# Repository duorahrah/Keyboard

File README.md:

# Custom 75% Mechanical Keyboard
Designed and built fully custom mechanical keyboard end-to-end, PCB design (KiCad), case design (Onshape) and 3D printing, and firmware (QMK on RP2040).\

## PCB Design

<br/>
-	Designed a RP2040-based custom mechanical keyboard PCB in KiCad with full keyboard matrix and USB-C connectivity
-	Includes full RP2040 support circuitry (crystal, QSPI flash, decoupling, reset and BOOTSEL)
-	Routed and manufactured the PCB

## Case Design

<br/>
-	Modeled custom case in Onshape, accounting for PCB mounting points, USB-C cutout, and switch plate clearance 

## Firmware
-	Developed custom QMK firmware for the keyboard, including multi-layer keymap and matrix/layout configuration to match the custom PCB design

## Challenges
-	USB and RP2040 debugging – I encountered an issue where the keyboard could not be detected by my computer while trying to flash the firmware. I was able to identify the issue as a short between the D+/D- connections through systematic multimeter-based debugging and fix it.
-	3D printer calibration - Case was printed using secondhand ELEGOO Neptune 4 Max, a printer which is known to be finnicky. I did research and looked at experiences from others who had the same printer to learn how to properly calibrate the printer, including replacing the bed springs with silicon spacers, and altering the printer’s configuration file to automatically level the bed and generate a printing mesh. 
-	Obtaining tools and materials – I was unable to gain access to public/free 3D printers over the summer, so I purchased a secondhand printer off Facebook Marketplace. The PCB and parts were ordered from JLCPCB and DigiKey (including $40 for international shipping D:). 

## Results
-	Successfully designed, manufactured, and assembled a working mechanical keyboard for daily use
-	Gained experience across PCB design, mechanical design, manufacturing, firmware development, and hardware debugging

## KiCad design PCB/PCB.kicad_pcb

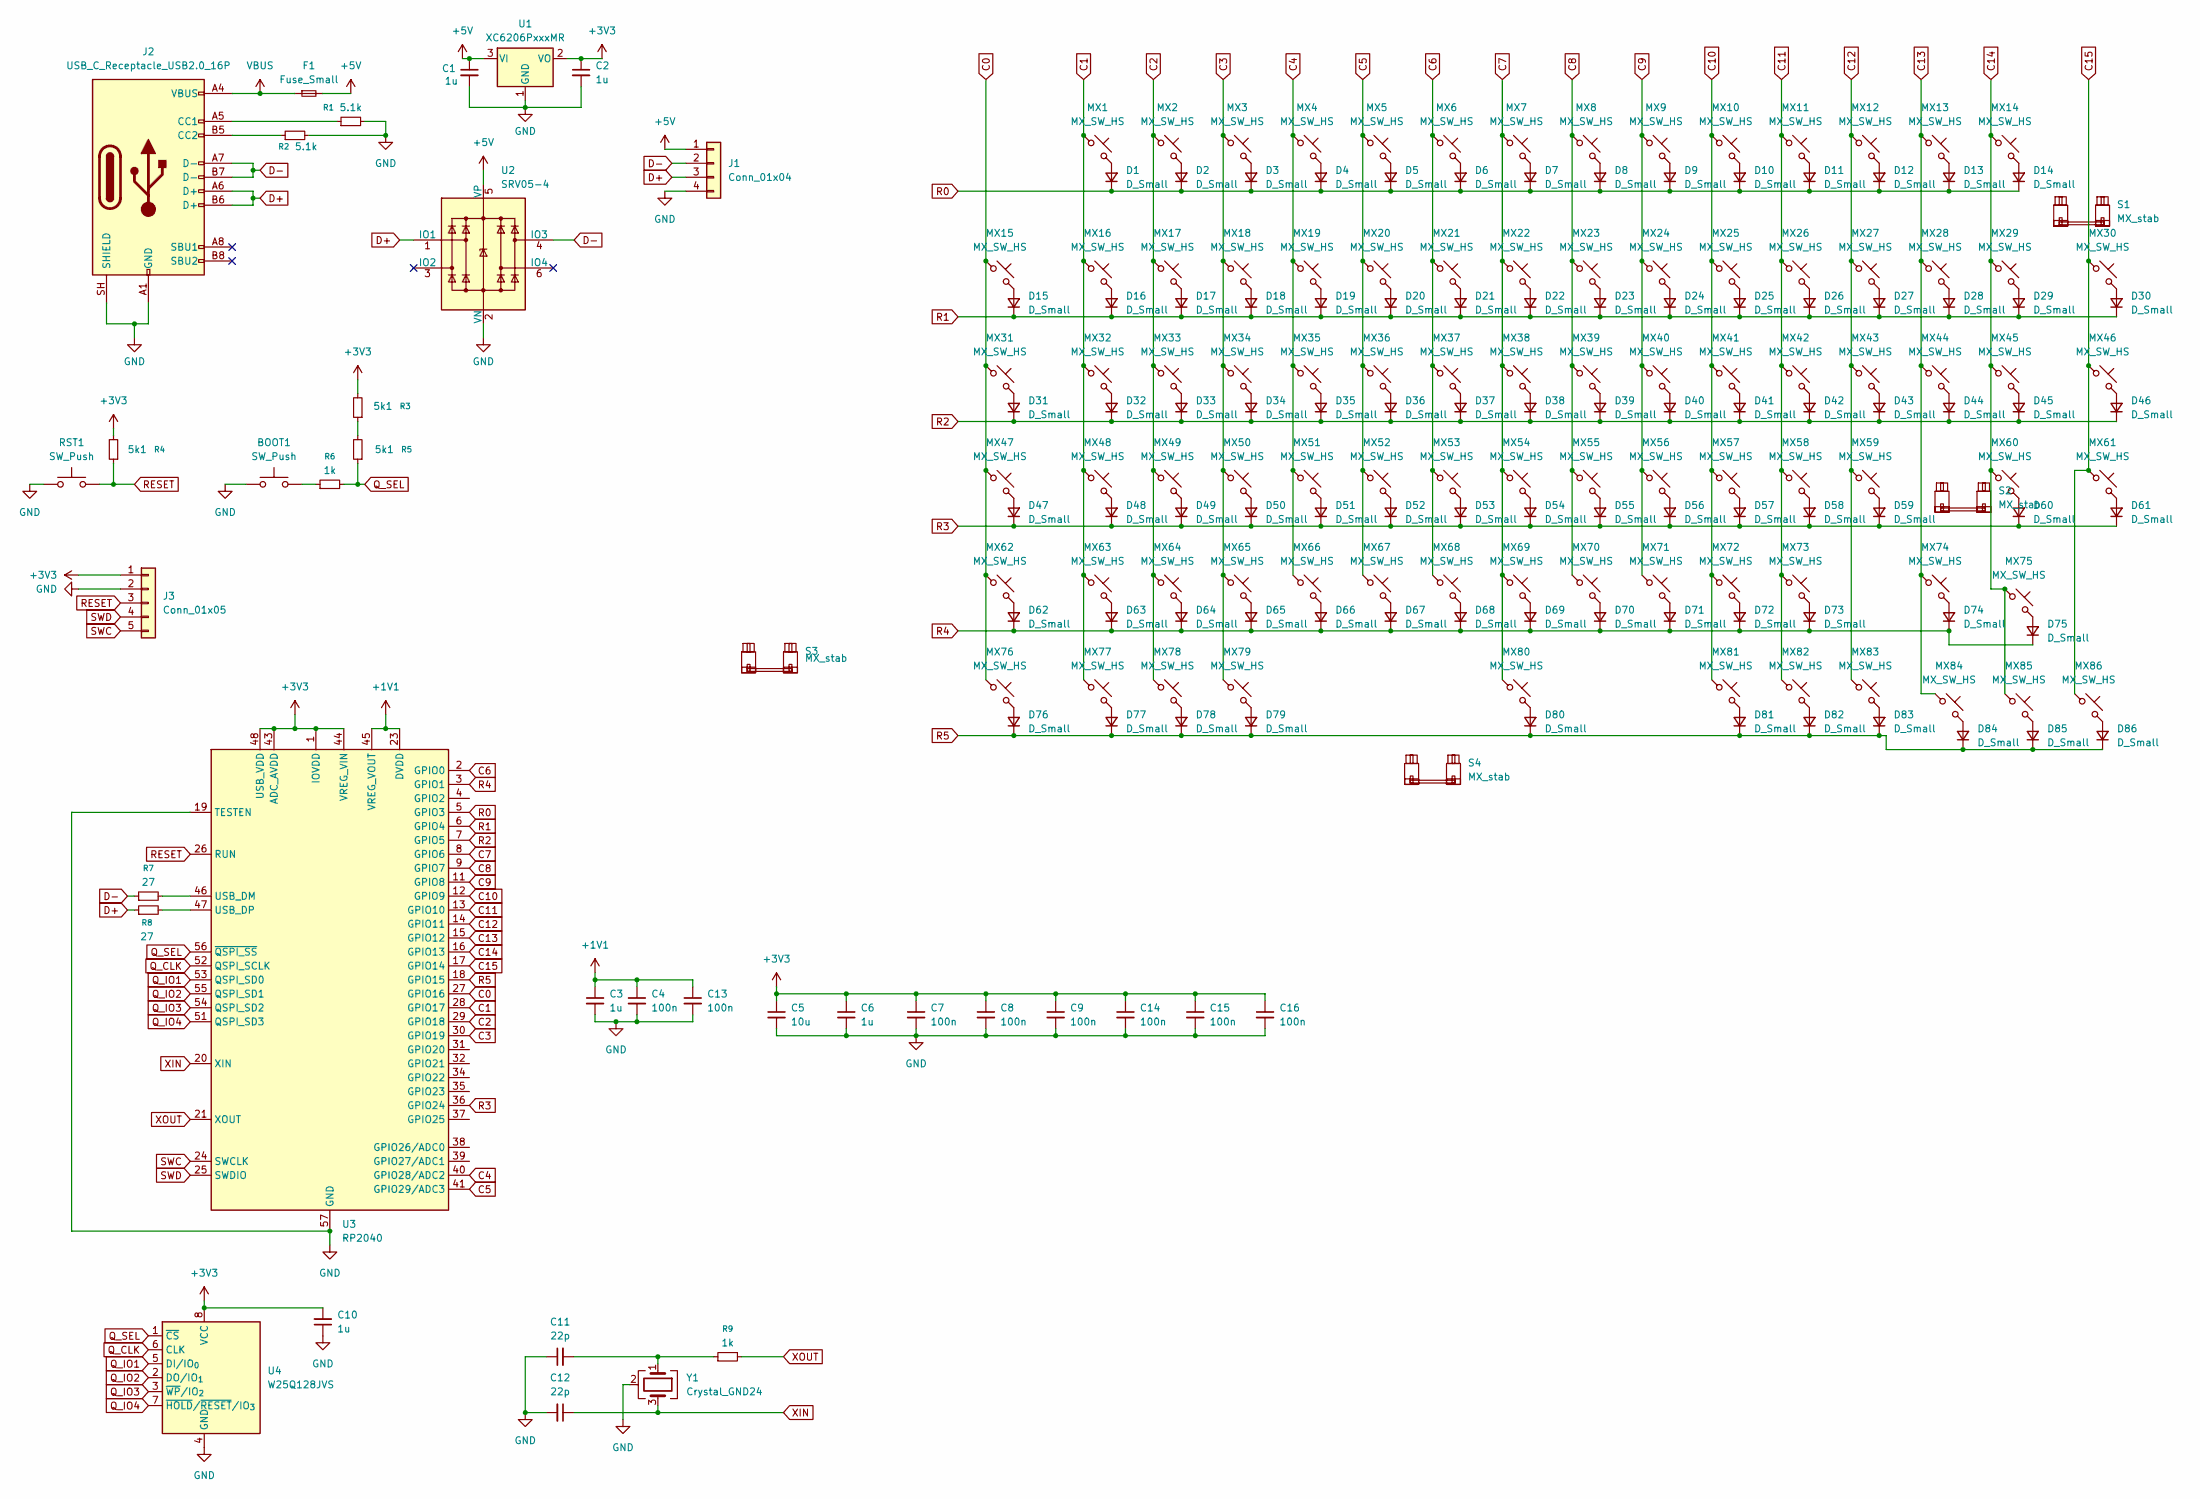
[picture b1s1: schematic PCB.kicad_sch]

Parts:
BOOT1: SW_Push; SW_SPST_TL3342
C1, C2, C3, C6, C10: 1u; C_0402_1005Metric
C4, C7, C8, C9, C13, C14, C15, C16: 100n; C_0402_1005Metric
C5: 10u; C_0603_1608Metric
C11, C12: 22p; C_0402_1005Metric
D1, D2, D3, D4, D5, D6, D7, D8, D9, D10, D11, D12, D13, D14, D15, D16, D17, D18, D19, D20, D21, D22, D23, D24, D25, D26, D27, D28, D29, D30, D31, D32, D33, D34, D35, D36, D37, D38, D39, D40, D41, D42, D43, D44, D45, D46, D47, D48, D49, D50, D51, D52, D53, D54, D55, D56, D57, D58, D59, D60, D61, D62, D63, D64, D65, D66, D67, D68, D69, D70, D71, D72, D73, D74, D75, D76, D77, D78, D79, D80, D81, D82, D83, D84, D85, D86: D_Small; D_SOD-123
F1: Fuse_Small; Fuse_1206_3216Metric
J1: Conn_01x04; JST_SH_SM04B-SRSS-TB_1x04-1MP_P1.00mm_Horizontal
J2: USB_C_Receptacle_USB2.0_16P; USB_C_Receptacle_HRO_TYPE-C-31-M-12
J3: Conn_01x05; PinHeader_1x05_P2.54mm_Vertical
MX1, MX2, MX3, MX4, MX5, MX6, MX7, MX8, MX9, MX10, MX11, MX12, MX13, MX14, MX15, MX16, MX17, MX18, MX19, MX20, MX21, MX22, MX23, MX24, MX25, MX26, MX27, MX28, MX29, MX30, MX31, MX33, MX34, MX35, MX36, MX37, MX38, MX39, MX40, MX41, MX42, MX43, MX44, MX46, MX47, MX49, MX50, MX51, MX52, MX53, MX54, MX55, MX56, MX57, MX58, MX59, MX60, MX61, MX62, MX63, MX64, MX65, MX66, MX67, MX68, MX69, MX70, MX71, MX72, MX73, MX75, MX76, MX80, MX81, MX82, MX83, MX84, MX85, MX86: MX_SW_HS; SW_MX_HS_CPG151101S11_1u
MX32, MX45: MX_SW_HS; SW_MX_HS_CPG151101S11_1.5u
MX48, MX74: MX_SW_HS; SW_MX_HS_CPG151101S11_1.75u
MX77, MX78, MX79: MX_SW_HS; SW_MX_HS_KS-2P02B01-01_1.25u
R1, R2: 5.1k; R_0402_1005Metric
R3, R4, R5: 5k1; R_0402_1005Metric
R6, R9: 1k; R_0402_1005Metric
R7, R8: 27; R_0402_1005Metric
RST1: SW_Push; SW_SPST_TL3342
S1: MX_stab; STAB_MX_P_2u
S2, S3: MX_stab; STAB_MX_P_2.25u
S4: MX_stab; STAB_MX_P_6.25u
U1: XC6206PxxxMR; SOT-23-3
U2: SRV05-4; SOT-23-6
U3: RP2040; QFN-56-1EP_7x7mm_P0.4mm_EP3.2x3.2mm
U4: W25Q128JVS; SOIC-8_5.3x5.3mm_P1.27mm
Y1: Crystal_GND24; Crystal_SMD_3225-4Pin_3.2x2.5mm

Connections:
+1V1: C3.1, C4.1, C13.1, U3.23 (DVDD), U3.45 (VREG_VOUT), U3.50 (DVDD)
+3V3: C2.1, C5.1, C6.1, C7.1, C8.1, C9.1, C10.2, C14.1, C15.1, C16.1, J3.1, R3.2, R4.2, U1.2 (VO), U3.1 (IOVDD), U3.10 (IOVDD), U3.22 (IOVDD), U3.33 (IOVDD), U3.42 (IOVDD), U3.43 (ADC_AVDD), U3.44 (VREG_VIN), U3.48 (USB_VDD), U3.49 (IOVDD), U4.8 (VCC)
+5V: C1.1, F1.2, J1.1, U1.3 (VI), U2.5 (VP)
C0: MX15.1, MX31.1, MX47.1, MX62.1, MX76.1, U3.27 (GPIO16)
C1: MX1.1, MX16.1, MX32.1, MX48.1, MX63.1, MX77.1, U3.28 (GPIO17)
C2: MX2.1, MX17.1, MX33.1, MX49.1, MX64.1, MX78.1, U3.29 (GPIO18)
C3: MX3.1, MX18.1, MX34.1, MX50.1, MX65.1, MX79.1, U3.30 (GPIO19)
C4: MX4.1, MX19.1, MX35.1, MX51.1, MX66.1, U3.40 (GPIO28/ADC2)
C5: MX5.1, MX20.1, MX36.1, MX52.1, MX67.1, U3.41 (GPIO29/ADC3)
C6: MX6.1, MX21.1, MX37.1, MX53.1, MX68.1, U3.2 (GPIO0)
C7: MX7.1, MX22.1, MX38.1, MX54.1, MX69.1, MX80.1, U3.8 (GPIO6)
C8: MX8.1, MX23.1, MX39.1, MX55.1, MX70.1, U3.9 (GPIO7)
C9: MX9.1, MX24.1, MX40.1, MX56.1, MX71.1, U3.11 (GPIO8)
C10: MX10.1, MX25.1, MX41.1, MX57.1, MX72.1, MX81.1, U3.12 (GPIO9)
C11: MX11.1, MX26.1, MX42.1, MX58.1, MX73.1, MX82.1, U3.13 (GPIO10)
C12: MX12.1, MX27.1, MX43.1, MX59.1, MX83.1, U3.14 (GPIO11)
C13: MX13.1, MX28.1, MX44.1, MX74.1, MX84.1, U3.15 (GPIO12)
C14: MX14.1, MX29.1, MX45.1, MX60.1, MX75.1, MX85.1, U3.16 (GPIO13)
C15: MX30.1, MX46.1, MX61.1, MX86.1, U3.17 (GPIO14)
D+: J1.3, J2.A6 (D+), J2.B6 (D+), R8.1, U2.1 (IO1)
D-: J1.2, J2.A7 (D-), J2.B7 (D-), R7.1, U2.4 (IO3)
GND: BOOT1.1, C1.2, C2.2, C3.2, C4.2, C5.2, C6.2, C7.2, C8.2, C9.2, C10.1, C11.1, C12.2, C13.2, C14.2, C15.2, C16.2, J1.4, J2.A1 (GND), J2.A12 (GND), J2.B1 (GND), J2.B12 (GND), J2.SH (SHIELD), J3.2, R1.2, R2.2, RST1.1, U1.1 (GND), U2.2 (VN), U3.19 (TESTEN), U3.57 (GND), U4.4 (GND), Y1.2 (G), Y1.4 (G)
unnamed: BOOT1.2, R6.1
unnamed: C11.2, R9.1, Y1.1
unnamed: D1.2 (A), MX1.2
unnamed: D2.2 (A), MX2.2
unnamed: D3.2 (A), MX3.2
unnamed: D4.2 (A), MX4.2
unnamed: D5.2 (A), MX5.2
unnamed: D6.2 (A), MX6.2
unnamed: D7.2 (A), MX7.2
unnamed: D8.2 (A), MX8.2
unnamed: D9.2 (A), MX9.2
unnamed: D10.2 (A), MX10.2
unnamed: D11.2 (A), MX11.2
unnamed: D12.2 (A), MX12.2
unnamed: D13.2 (A), MX13.2
unnamed: D14.2 (A), MX14.2
unnamed: D15.2 (A), MX15.2
unnamed: D16.2 (A), MX16.2
unnamed: D17.2 (A), MX17.2
unnamed: D18.2 (A), MX18.2
unnamed: D19.2 (A), MX19.2
unnamed: D20.2 (A), MX20.2
unnamed: D21.2 (A), MX21.2
unnamed: D22.2 (A), MX22.2
unnamed: D23.2 (A), MX23.2
unnamed: D24.2 (A), MX24.2
unnamed: D25.2 (A), MX25.2
unnamed: D26.2 (A), MX26.2
unnamed: D27.2 (A), MX27.2
unnamed: D28.2 (A), MX28.2
unnamed: D29.2 (A), MX29.2
unnamed: D30.2 (A), MX30.2
unnamed: D31.2 (A), MX31.2
unnamed: D32.2 (A), MX32.2
unnamed: D33.2 (A), MX33.2
unnamed: D34.2 (A), MX34.2
unnamed: D35.2 (A), MX35.2
unnamed: D36.2 (A), MX36.2
unnamed: D37.2 (A), MX37.2
unnamed: D38.2 (A), MX38.2
unnamed: D39.2 (A), MX39.2
unnamed: D40.2 (A), MX40.2
unnamed: D41.2 (A), MX41.2
unnamed: D42.2 (A), MX42.2
unnamed: D43.2 (A), MX43.2
unnamed: D44.2 (A), MX44.2
unnamed: D45.2 (A), MX45.2
unnamed: D46.2 (A), MX46.2
unnamed: D47.2 (A), MX47.2
unnamed: D48.2 (A), MX48.2
unnamed: D49.2 (A), MX49.2
unnamed: D50.2 (A), MX50.2
unnamed: D51.2 (A), MX51.2
unnamed: D52.2 (A), MX52.2
unnamed: D53.2 (A), MX53.2
unnamed: D54.2 (A), MX54.2
unnamed: D55.2 (A), MX55.2
unnamed: D56.2 (A), MX56.2
unnamed: D57.2 (A), MX57.2
unnamed: D58.2 (A), MX58.2
unnamed: D59.2 (A), MX59.2
unnamed: D60.2 (A), MX60.2
unnamed: D61.2 (A), MX61.2
unnamed: D62.2 (A), MX62.2
unnamed: D63.2 (A), MX63.2
unnamed: D64.2 (A), MX64.2
unnamed: D65.2 (A), MX65.2
unnamed: D66.2 (A), MX66.2
unnamed: D67.2 (A), MX67.2
unnamed: D68.2 (A), MX68.2
unnamed: D69.2 (A), MX69.2
unnamed: D70.2 (A), MX70.2
unnamed: D71.2 (A), MX71.2
unnamed: D72.2 (A), MX72.2
unnamed: D73.2 (A), MX73.2
unnamed: D74.2 (A), MX74.2
unnamed: D75.2 (A), MX75.2
unnamed: D76.2 (A), MX76.2
unnamed: D77.2 (A), MX77.2
unnamed: D78.2 (A), MX78.2
unnamed: D79.2 (A), MX79.2
unnamed: D80.2 (A), MX80.2
unnamed: D81.2 (A), MX81.2
unnamed: D82.2 (A), MX82.2
unnamed: D83.2 (A), MX83.2
unnamed: D84.2 (A), MX84.2
unnamed: D85.2 (A), MX85.2
unnamed: D86.2 (A), MX86.2
unnamed: J2.A5 (CC1), R1.1
unnamed: J2.B5 (CC2), R2.1
unnamed: R3.1, R5.2
unnamed: R7.2, U3.46 (USB_DM)
unnamed: R8.2, U3.47 (USB_DP)
Q_CLK: U3.52 (QSPI_SCLK), U4.6 (CLK)
Q_IO1: U3.53 (QSPI_SD0), U4.5 (DI/IO_{0})
Q_IO2: U3.55 (QSPI_SD1), U4.2 (DO/IO_{1})
Q_IO3: U3.54 (QSPI_SD2), U4.3 (~WP/IO_{2})
Q_IO4: U3.51 (QSPI_SD3), U4.7 (~HOLD/~RESET/IO_{3})
Q_SEL: R5.1, R6.2, U3.56 (~QSPI_SS), U4.1 (~CS)
R0: D1.1 (K), D2.1 (K), D3.1 (K), D4.1 (K), D5.1 (K), D6.1 (K), D7.1 (K), D8.1 (K), D9.1 (K), D10.1 (K), D11.1 (K), D12.1 (K), D13.1 (K), D14.1 (K), U3.5 (GPIO3)
R1: D15.1 (K), D16.1 (K), D17.1 (K), D18.1 (K), D19.1 (K), D20.1 (K), D21.1 (K), D22.1 (K), D23.1 (K), D24.1 (K), D25.1 (K), D26.1 (K), D27.1 (K), D28.1 (K), D29.1 (K), D30.1 (K), U3.6 (GPIO4)
R2: D31.1 (K), D32.1 (K), D33.1 (K), D34.1 (K), D35.1 (K), D36.1 (K), D37.1 (K), D38.1 (K), D39.1 (K), D40.1 (K), D41.1 (K), D42.1 (K), D43.1 (K), D44.1 (K), D45.1 (K), D46.1 (K), U3.7 (GPIO5)
R3: D47.1 (K), D48.1 (K), D49.1 (K), D50.1 (K), D51.1 (K), D52.1 (K), D53.1 (K), D54.1 (K), D55.1 (K), D56.1 (K), D57.1 (K), D58.1 (K), D59.1 (K), D60.1 (K), D61.1 (K), U3.36 (GPIO24)
R4: D62.1 (K), D63.1 (K), D64.1 (K), D65.1 (K), D66.1 (K), D67.1 (K), D68.1 (K), D69.1 (K), D70.1 (K), D71.1 (K), D72.1 (K), D73.1 (K), D74.1 (K), D75.1 (K), U3.3 (GPIO1)
R5: D76.1 (K), D77.1 (K), D78.1 (K), D79.1 (K), D80.1 (K), D81.1 (K), D82.1 (K), D83.1 (K), D84.1 (K), D85.1 (K), D86.1 (K), U3.18 (GPIO15)
RESET: J3.3, R4.1, RST1.2, U3.26 (RUN)
SWC: J3.5, U3.24 (SWCLK)
SWD: J3.4, U3.25 (SWDIO)
VBUS: F1.1, J2.A4 (VBUS), J2.A9 (VBUS), J2.B4 (VBUS), J2.B9 (VBUS)
XIN: C12.1, U3.20 (XIN), Y1.3
XOUT: R9.2, U3.21 (XOUT)

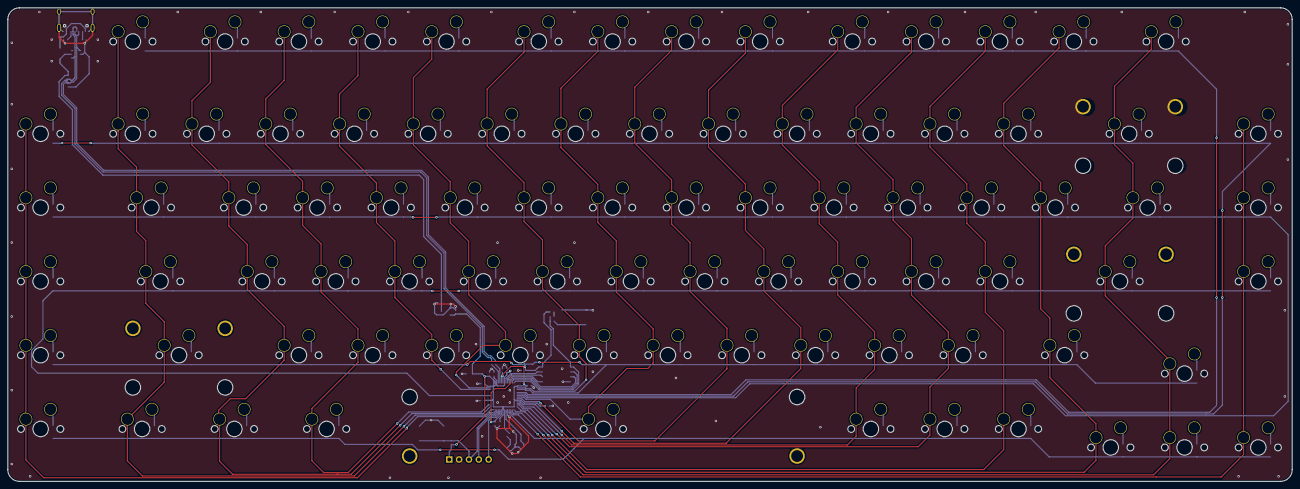
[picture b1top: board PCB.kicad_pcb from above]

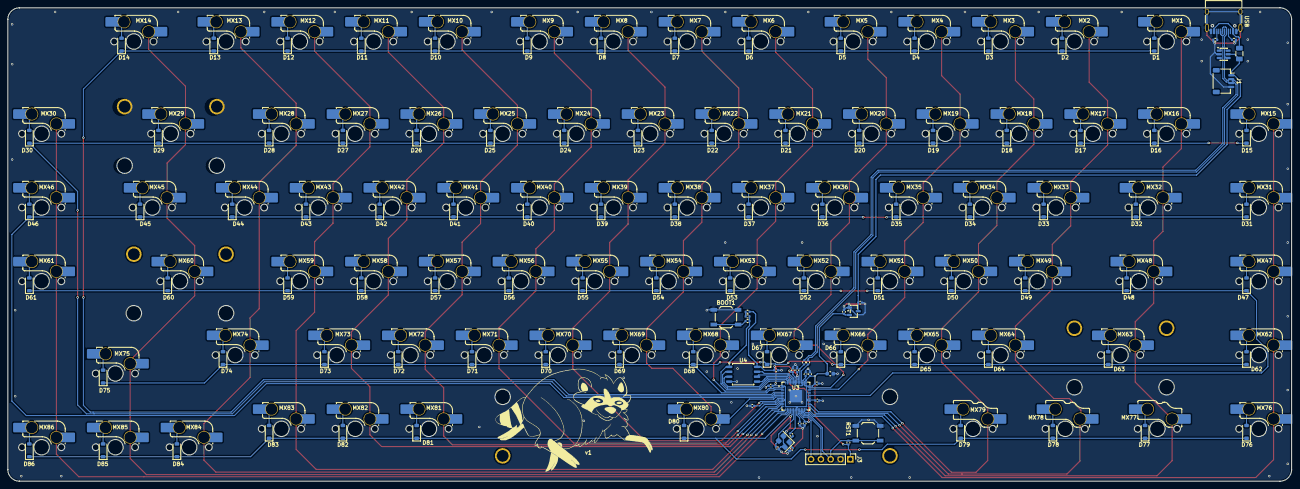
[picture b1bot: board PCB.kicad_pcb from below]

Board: 2 copper layers, 331.5 x 122.2 mm, 212 parts (209 on the bottom side), 133 nets.

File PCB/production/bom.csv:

Designator,Footprint,Quantity,Value,LCSC Part #
"BOOT1, RST1",SW_SPST_TL3342,2,SW_Push,
"C1, C10, C2, C3, C6",0402,5,1u,
"C11, C12",0402,2,22p,
"C13, C14, C15, C16, C4, C7, C8, C9",0402,8,100n,
C5,0603,1,10u,
"D1, D10, D11, D12, D13, D14, D15, D16, D17, D18, D19, D2, D20, D21, D22, D23, D24, D25, D26, D27, D28, D29, D3, D30, D31, D32, D33, D34, D35, D36, D37, D38, D39, D4, D40, D41, D42, D43, D44, D45, D46, D47, D48, D49, D5, D50, D51, D52, D53, D54, D55, D56, D57, D58, D59, D6, D60, D61, D62, D63, D64, D65, D66, D67, D68, D69, D7, D70, D71, D72, D73, D74, D75, D76, D77, D78, D79, D8, D80, D81, D82, D83, D84, D85, D86, D9",D_SOD-123,86,D_Small,
F1,1206,1,Fuse_Small,
J1,JST_SH_SM04B-SRSS-TB_1x04-1MP_P1.00mm_Horizontal,1,Conn_01x04,
J2,USB_C_Receptacle_HRO_TYPE-C-31-M-12,1,USB_C_Receptacle_USB2.0_16P,
J3,PinHeader_1x05_P2.54mm_Vertical,1,Conn_01x05,
"MX1, MX10, MX11, MX12, MX13, MX14, MX15, MX16, MX17, MX18, MX19, MX2, MX20, MX21, MX22, MX23, MX24, MX25, MX26, MX27, MX28, MX29, MX3, MX30, MX31, MX33, MX34, MX35, MX36, MX37, MX38, MX39, MX4, MX40, MX41, MX42, MX43, MX44, MX46, MX47, MX49, MX5, MX50, MX51, MX52, MX53, MX54, MX55, MX56, MX57, MX58, MX59, MX6, MX60, MX61, MX62, MX63, MX64, MX65, MX66, MX67, MX68, MX69, MX7, MX70, MX71, MX72, MX73, MX75, MX76, MX8, MX80, MX81, MX82, MX83, MX84, MX85, MX86, MX9",SW_MX_HS_CPG151101S11_1u,79,MX_SW_HS,
"MX32, MX45",SW_MX_HS_CPG151101S11_1.5u,2,MX_SW_HS,
"MX48, MX74",SW_MX_HS_CPG151101S11_1.75u,2,MX_SW_HS,
"MX77, MX78, MX79",SW_MX_HS_KS-2P02B01-01_1.25u,3,MX_SW_HS,
"R1, R2",0402,2,5.1k,
"R3, R4, R5",0402,3,5k1,
"R6, R9",0402,2,1k,
"R7, R8",0402,2,27,
S1,STAB_MX_P_2u,1,MX_stab,
"S2, S3",STAB_MX_P_2.25u,2,MX_stab,
S4,STAB_MX_P_6.25u,1,MX_stab,
U1,SOT-23-3,1,XC6206PxxxMR,
U2,SOT-23-6,1,SRV05-4,
U3,QFN-56-1EP_7x7mm_P0.4mm_EP3.2x3.2mm,1,RP2040,
U4,SOIC-8_5.3x5.3mm_P1.27mm,1,W25Q128JVS,
Y1,Crystal_SMD_3225-4Pin_3.2x2.5mm,1,Crystal_GND24,
